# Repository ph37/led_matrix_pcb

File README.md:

# 32x16 LED Array PCB using 788BS

KiKad 5.1 files for the design of an LED matrix. The board has been manufactured by PCB Way and is
working.

The design is based around 788BS LED modules, which each contain 8x8 red LEDs in a common cathode
configuration.

While physically a 16 row and 32 column design, it is logically organised as 8 rows and 64
columns. Logical row N drives physical rows N and N+8.

Uses a 3-pin header to drive a series of 74HC595 shift registers. First shift register is connected to a 
74HC238 3-to-8 decoder to provide hardware enforced one-hot enable of rows. Rows are driven by a PMV16XN 
SMT power MOSFET to provide enough current to drive 32 LED columns.

Another eight 8-bit shift registers provide control over the 64 columns, with each column
using a 680 ohm resistor to limit current. Brightness of individual LEDs can be supported
externally by reprogramming the shift register and pulse-width-modulating the on-time for
each column.

## Notes

Board layout is intended for manufacture by PCB Way and follows PCB Way design rules. Please check
compatibility with design rules for any other PCB house.

Board is a very basic design and intended for low frequency operation only. In particular there is
no ground plane, which I plan to include in a future revision.

Take care with 788BS parts, I recommend testing them before soldering onto the board. 
The first board I've built has a short circuit inside one of 788BS components, are these 
are difficult to remove as the pins are underneath the package.

## Errata

v01 of the board transposed rows 6 and 7 on the included 788BS symbol. This can be resolved
by transposing the data for these rows in software before driving the serial interface.

## Future

I plan to release C drivers for Paspberry Pi Pico. Eventually I plan to migrate the IO the Pico's
programmable IO.

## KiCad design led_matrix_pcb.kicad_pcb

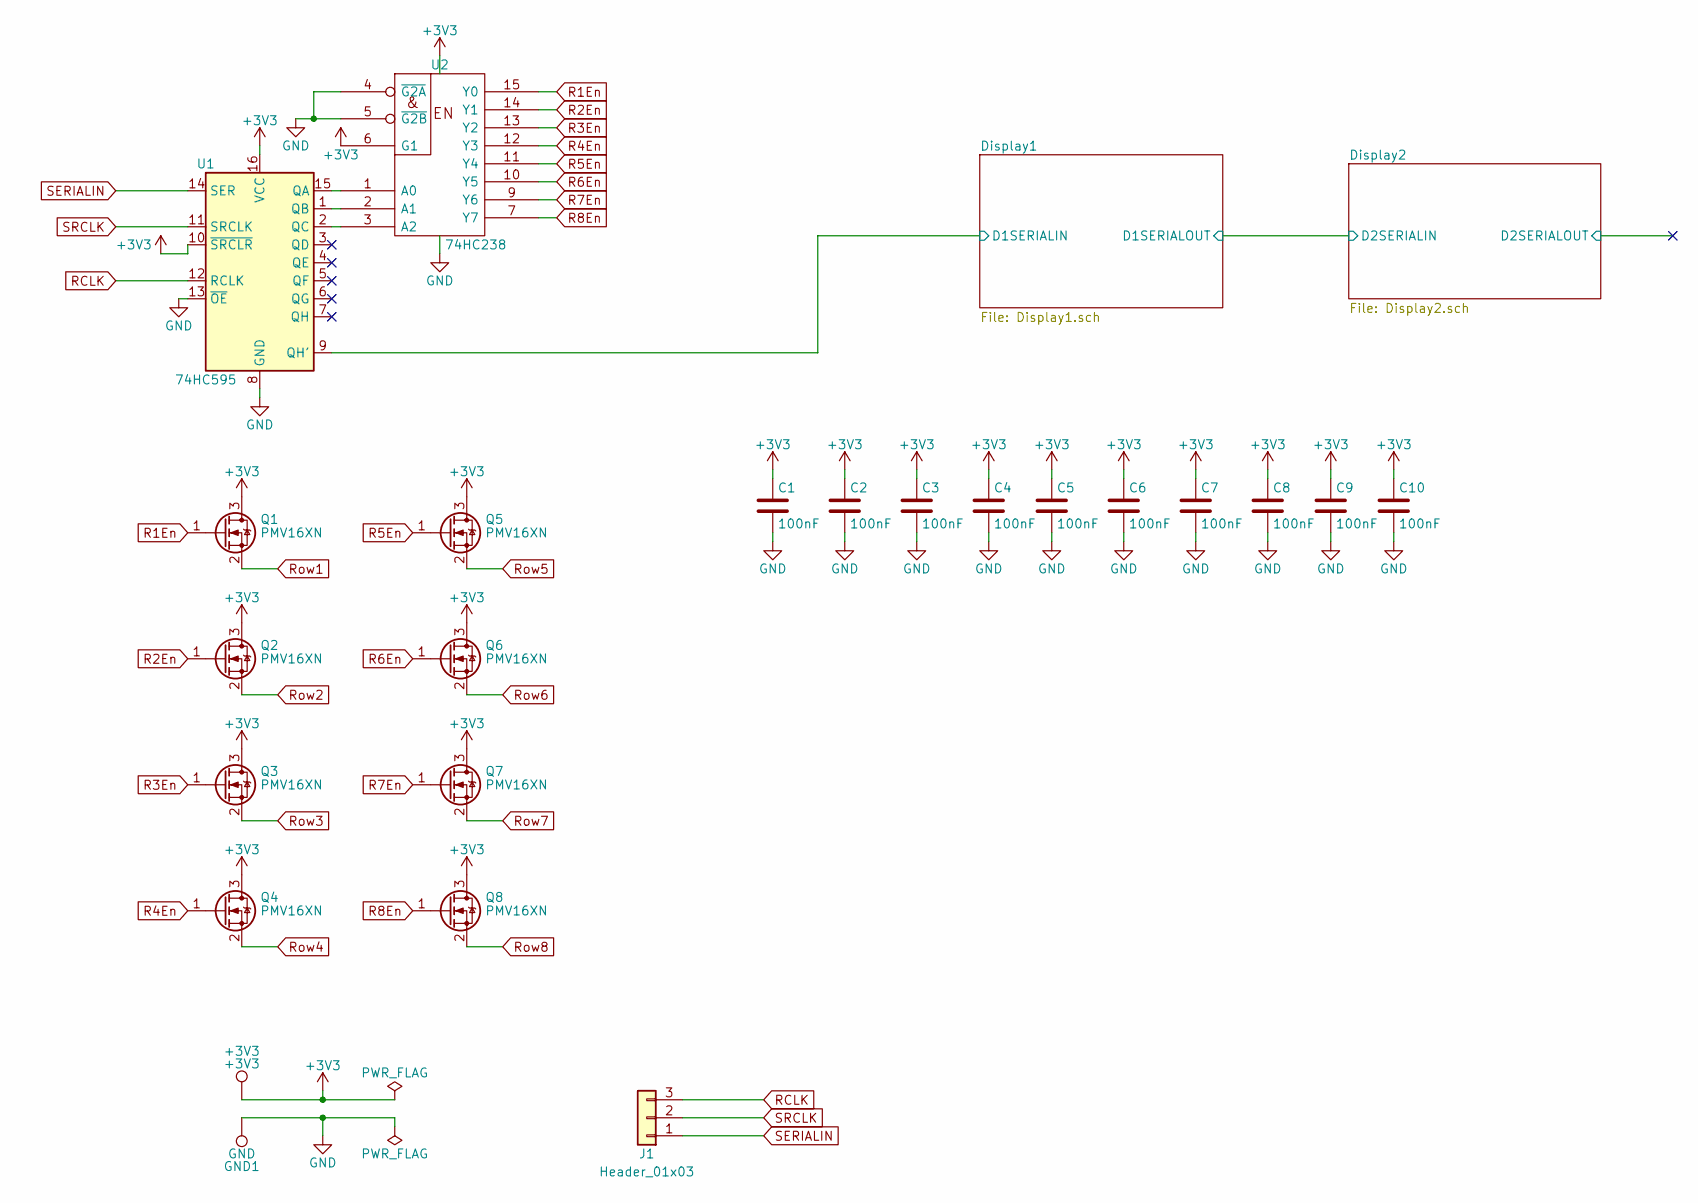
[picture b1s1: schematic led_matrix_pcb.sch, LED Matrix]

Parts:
+3V3: +3V3; TestPoint_Pad_D4.0mm
C1, C2, C3, C4, C5, C6, C7, C8, C9, C10: 100nF; C_Disc_D10.0mm_W2.5mm_P5.00mm
GND1: GND; TestPoint_Pad_D4.0mm
J1: Header_01x03; PinHeader_1x03_P2.54mm_Vertical
Q1, Q2, Q3, Q4, Q5, Q6, Q7, Q8: PMV16XN; SOT-23
U1: 74HC595; DIP-16_W7.62mm
U2: 74HC238; DIP-16_W7.62mm

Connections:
+3V3: +3V3.1, C1.1, C2.1, C3.1, C4.1, C5.1, C6.1, C7.1, C8.1, C9.1, C10.1, Q1.3 (D), Q2.3 (D), Q3.3 (D), Q4.3 (D), Q5.3 (D), Q6.3 (D), Q7.3 (D), Q8.3 (D), U1.10 (~SRCLR), U1.16 (VCC), U2.6 (G1), U2.16 (VCC); also elsewhere on the board
/Display1/D1SERIALIN: U1.9 (QH'); also elsewhere on the board
GND: C1.2, C2.2, C3.2, C4.2, C5.2, C6.2, C7.2, C8.2, C9.2, C10.2, GND1.1, U1.8 (GND), U1.13 (~OE), U2.4 (~G2A), U2.5 (~G2B), U2.8 (GND); also elsewhere on the board
unnamed: U1.1 (QB), U2.2 (A1)
unnamed: U1.2 (QC), U2.3 (A2)
unnamed: U1.15 (QA), U2.1 (A0)
R1En: Q1.1 (G), U2.15 (Y0)
R2En: Q2.1 (G), U2.14 (Y1)
R3En: Q3.1 (G), U2.13 (Y2)
R4En: Q4.1 (G), U2.12 (Y3)
R5En: Q5.1 (G), U2.11 (Y4)
R6En: Q6.1 (G), U2.10 (Y5)
R7En: Q7.1 (G), U2.9 (Y6)
R8En: Q8.1 (G), U2.7 (Y7)
RCLK: J1.3, U1.12 (RCLK); also elsewhere on the board
Row1: Q1.2 (S); also elsewhere on the board
Row2: Q2.2 (S); also elsewhere on the board
Row3: Q3.2 (S); also elsewhere on the board
Row4: Q4.2 (S); also elsewhere on the board
Row5: Q5.2 (S); also elsewhere on the board
Row6: Q6.2 (S); also elsewhere on the board
Row7: Q7.2 (S); also elsewhere on the board
Row8: Q8.2 (S); also elsewhere on the board
SERIALIN: J1.1, U1.14 (SER)
SRCLK: J1.2, U1.11 (SRCLK); also elsewhere on the board

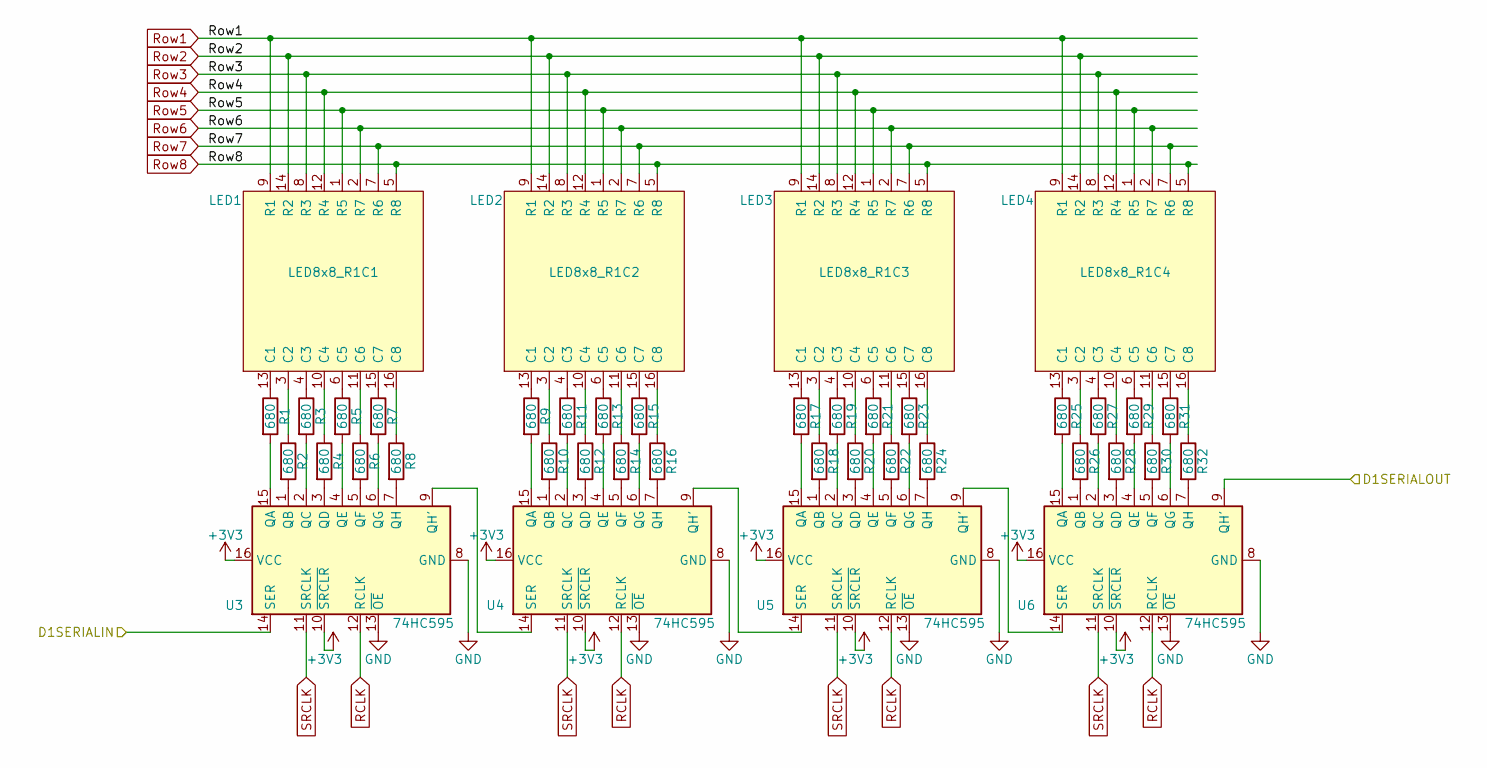
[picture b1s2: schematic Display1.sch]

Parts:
LED1: LED8x8_R1C1; 788BS
LED2: LED8x8_R1C2; 788BS
LED3: LED8x8_R1C3; 788BS
LED4: LED8x8_R1C4; 788BS
R1, R2, R3, R4, R5, R6, R7, R8, R9, R10, R11, R12, R13, R14, R15, R16, R17, R18, R19, R20, R21, R22, R23, R24, R25, R26, R27, R28, R29, R30, R31, R32: 680; R_Axial_DIN0204_L3.6mm_D1.6mm_P5.08mm_Horizontal
U3, U4, U5, U6: 74HC595; DIP-16_W7.62mm

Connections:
+3V3: U3.10 (~SRCLR), U3.16 (VCC), U4.10 (~SRCLR), U4.16 (VCC), U5.10 (~SRCLR), U5.16 (VCC), U6.10 (~SRCLR), U6.16 (VCC); also elsewhere on the board
/Display1/D1SERIALIN: U3.14 (SER); also elsewhere on the board
/Display1/D1SERIALOUT: U6.9 (QH'); also elsewhere on the board
GND: U3.8 (GND), U3.13 (~OE), U4.8 (GND), U4.13 (~OE), U5.8 (GND), U5.13 (~OE), U6.8 (GND), U6.13 (~OE); also elsewhere on the board
unnamed: LED1.3 (C2), R2.1
unnamed: LED1.4 (C3), R3.1
unnamed: LED1.6 (C5), R5.1
unnamed: LED1.10 (C4), R4.1
unnamed: LED1.11 (C6), R6.1
unnamed: LED1.13 (C1), R1.1
unnamed: LED1.15 (C7), R7.1
unnamed: LED1.16 (C8), R8.1
unnamed: LED2.3 (C2), R10.1
unnamed: LED2.4 (C3), R11.1
unnamed: LED2.6 (C5), R13.1
unnamed: LED2.10 (C4), R12.1
unnamed: LED2.11 (C6), R14.1
unnamed: LED2.13 (C1), R9.1
unnamed: LED2.15 (C7), R15.1
unnamed: LED2.16 (C8), R16.1
unnamed: LED3.3 (C2), R18.1
unnamed: LED3.4 (C3), R19.1
unnamed: LED3.6 (C5), R21.1
unnamed: LED3.10 (C4), R20.1
unnamed: LED3.11 (C6), R22.1
unnamed: LED3.13 (C1), R17.1
unnamed: LED3.15 (C7), R23.1
unnamed: LED3.16 (C8), R24.1
unnamed: LED4.3 (C2), R26.1
unnamed: LED4.4 (C3), R27.1
unnamed: LED4.6 (C5), R29.1
unnamed: LED4.10 (C4), R28.1
unnamed: LED4.11 (C6), R30.1
unnamed: LED4.13 (C1), R25.1
unnamed: LED4.15 (C7), R31.1
unnamed: LED4.16 (C8), R32.1
unnamed: R1.2, U3.15 (QA)
unnamed: R2.2, U3.1 (QB)
unnamed: R3.2, U3.2 (QC)
unnamed: R4.2, U3.3 (QD)
unnamed: R5.2, U3.4 (QE)
unnamed: R6.2, U3.5 (QF)
unnamed: R7.2, U3.6 (QG)
unnamed: R8.2, U3.7 (QH)
unnamed: R9.2, U4.15 (QA)
unnamed: R10.2, U4.1 (QB)
unnamed: R11.2, U4.2 (QC)
unnamed: R12.2, U4.3 (QD)
unnamed: R13.2, U4.4 (QE)
unnamed: R14.2, U4.5 (QF)
unnamed: R15.2, U4.6 (QG)
unnamed: R16.2, U4.7 (QH)
unnamed: R17.2, U5.15 (QA)
unnamed: R18.2, U5.1 (QB)
unnamed: R19.2, U5.2 (QC)
unnamed: R20.2, U5.3 (QD)
unnamed: R21.2, U5.4 (QE)
unnamed: R22.2, U5.5 (QF)
unnamed: R23.2, U5.6 (QG)
unnamed: R24.2, U5.7 (QH)
unnamed: R25.2, U6.15 (QA)
unnamed: R26.2, U6.1 (QB)
unnamed: R27.2, U6.2 (QC)
unnamed: R28.2, U6.3 (QD)
unnamed: R29.2, U6.4 (QE)
unnamed: R30.2, U6.5 (QF)
unnamed: R31.2, U6.6 (QG)
unnamed: R32.2, U6.7 (QH)
unnamed: U3.9 (QH'), U4.14 (SER)
unnamed: U4.9 (QH'), U5.14 (SER)
unnamed: U5.9 (QH'), U6.14 (SER)
RCLK: U3.12 (RCLK), U4.12 (RCLK), U5.12 (RCLK), U6.12 (RCLK); also elsewhere on the board
Row1: LED1.9 (R1), LED2.9 (R1), LED3.9 (R1), LED4.9 (R1); also elsewhere on the board
Row2: LED1.14 (R2), LED2.14 (R2), LED3.14 (R2), LED4.14 (R2); also elsewhere on the board
Row3: LED1.8 (R3), LED2.8 (R3), LED3.8 (R3), LED4.8 (R3); also elsewhere on the board
Row4: LED1.12 (R4), LED2.12 (R4), LED3.12 (R4), LED4.12 (R4); also elsewhere on the board
Row5: LED1.1 (R5), LED2.1 (R5), LED3.1 (R5), LED4.1 (R5); also elsewhere on the board
Row6: LED1.2 (R7), LED2.2 (R7), LED3.2 (R7), LED4.2 (R7); also elsewhere on the board
Row7: LED1.7 (R6), LED2.7 (R6), LED3.7 (R6), LED4.7 (R6); also elsewhere on the board
Row8: LED1.5 (R8), LED2.5 (R8), LED3.5 (R8), LED4.5 (R8); also elsewhere on the board
SRCLK: U3.11 (SRCLK), U4.11 (SRCLK), U5.11 (SRCLK), U6.11 (SRCLK); also elsewhere on the board

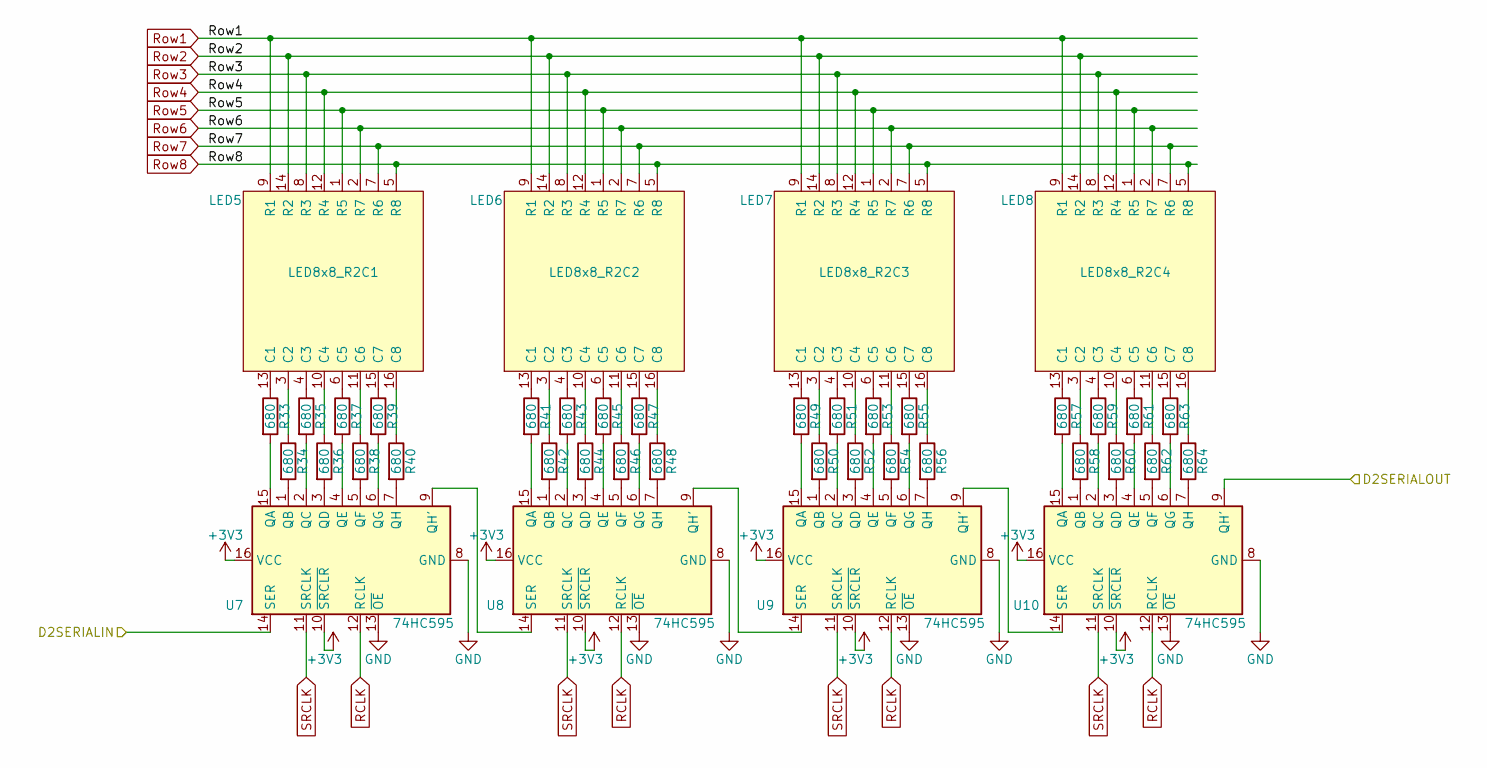
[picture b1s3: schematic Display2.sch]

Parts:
LED5: LED8x8_R2C1; 788BS
LED6: LED8x8_R2C2; 788BS
LED7: LED8x8_R2C3; 788BS
LED8: LED8x8_R2C4; 788BS
R33, R34, R35, R36, R37, R38, R39, R40, R41, R42, R43, R44, R45, R46, R47, R48, R49, R50, R51, R52, R53, R54, R55, R56, R57, R58, R59, R60, R61, R62, R63, R64: 680; R_Axial_DIN0204_L3.6mm_D1.6mm_P5.08mm_Horizontal
U7, U8, U9, U10: 74HC595; DIP-16_W7.62mm

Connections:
+3V3: U7.10 (~SRCLR), U7.16 (VCC), U8.10 (~SRCLR), U8.16 (VCC), U9.10 (~SRCLR), U9.16 (VCC), U10.10 (~SRCLR), U10.16 (VCC); also elsewhere on the board
/Display1/D1SERIALOUT: U7.14 (SER); also elsewhere on the board
/Display2/D2SERIALOUT: U10.9 (QH')
GND: U7.8 (GND), U7.13 (~OE), U8.8 (GND), U8.13 (~OE), U9.8 (GND), U9.13 (~OE), U10.8 (GND), U10.13 (~OE); also elsewhere on the board
unnamed: LED5.3 (C2), R34.1
unnamed: LED5.4 (C3), R35.1
unnamed: LED5.6 (C5), R37.1
unnamed: LED5.10 (C4), R36.1
unnamed: LED5.11 (C6), R38.1
unnamed: LED5.13 (C1), R33.1
unnamed: LED5.15 (C7), R39.1
unnamed: LED5.16 (C8), R40.1
unnamed: LED6.3 (C2), R42.1
unnamed: LED6.4 (C3), R43.1
unnamed: LED6.6 (C5), R45.1
unnamed: LED6.10 (C4), R44.1
unnamed: LED6.11 (C6), R46.1
unnamed: LED6.13 (C1), R41.1
unnamed: LED6.15 (C7), R47.1
unnamed: LED6.16 (C8), R48.1
unnamed: LED7.3 (C2), R50.1
unnamed: LED7.4 (C3), R51.1
unnamed: LED7.6 (C5), R53.1
unnamed: LED7.10 (C4), R52.1
unnamed: LED7.11 (C6), R54.1
unnamed: LED7.13 (C1), R49.1
unnamed: LED7.15 (C7), R55.1
unnamed: LED7.16 (C8), R56.1
unnamed: LED8.3 (C2), R58.1
unnamed: LED8.4 (C3), R59.1
unnamed: LED8.6 (C5), R61.1
unnamed: LED8.10 (C4), R60.1
unnamed: LED8.11 (C6), R62.1
unnamed: LED8.13 (C1), R57.1
unnamed: LED8.15 (C7), R63.1
unnamed: LED8.16 (C8), R64.1
unnamed: R33.2, U7.15 (QA)
unnamed: R34.2, U7.1 (QB)
unnamed: R35.2, U7.2 (QC)
unnamed: R36.2, U7.3 (QD)
unnamed: R37.2, U7.4 (QE)
unnamed: R38.2, U7.5 (QF)
unnamed: R39.2, U7.6 (QG)
unnamed: R40.2, U7.7 (QH)
unnamed: R41.2, U8.15 (QA)
unnamed: R42.2, U8.1 (QB)
unnamed: R43.2, U8.2 (QC)
unnamed: R44.2, U8.3 (QD)
unnamed: R45.2, U8.4 (QE)
unnamed: R46.2, U8.5 (QF)
unnamed: R47.2, U8.6 (QG)
unnamed: R48.2, U8.7 (QH)
unnamed: R49.2, U9.15 (QA)
unnamed: R50.2, U9.1 (QB)
unnamed: R51.2, U9.2 (QC)
unnamed: R52.2, U9.3 (QD)
unnamed: R53.2, U9.4 (QE)
unnamed: R54.2, U9.5 (QF)
unnamed: R55.2, U9.6 (QG)
unnamed: R56.2, U9.7 (QH)
unnamed: R57.2, U10.15 (QA)
unnamed: R58.2, U10.1 (QB)
unnamed: R59.2, U10.2 (QC)
unnamed: R60.2, U10.3 (QD)
unnamed: R61.2, U10.4 (QE)
unnamed: R62.2, U10.5 (QF)
unnamed: R63.2, U10.6 (QG)
unnamed: R64.2, U10.7 (QH)
unnamed: U7.9 (QH'), U8.14 (SER)
unnamed: U8.9 (QH'), U9.14 (SER)
unnamed: U9.9 (QH'), U10.14 (SER)
RCLK: U7.12 (RCLK), U8.12 (RCLK), U9.12 (RCLK), U10.12 (RCLK); also elsewhere on the board
Row1: LED5.9 (R1), LED6.9 (R1), LED7.9 (R1), LED8.9 (R1); also elsewhere on the board
Row2: LED5.14 (R2), LED6.14 (R2), LED7.14 (R2), LED8.14 (R2); also elsewhere on the board
Row3: LED5.8 (R3), LED6.8 (R3), LED7.8 (R3), LED8.8 (R3); also elsewhere on the board
Row4: LED5.12 (R4), LED6.12 (R4), LED7.12 (R4), LED8.12 (R4); also elsewhere on the board
Row5: LED5.1 (R5), LED6.1 (R5), LED7.1 (R5), LED8.1 (R5); also elsewhere on the board
Row6: LED5.2 (R7), LED6.2 (R7), LED7.2 (R7), LED8.2 (R7); also elsewhere on the board
Row7: LED5.7 (R6), LED6.7 (R6), LED7.7 (R6), LED8.7 (R6); also elsewhere on the board
Row8: LED5.5 (R8), LED6.5 (R8), LED7.5 (R8), LED8.5 (R8); also elsewhere on the board
SRCLK: U7.11 (SRCLK), U8.11 (SRCLK), U9.11 (SRCLK), U10.11 (SRCLK); also elsewhere on the board

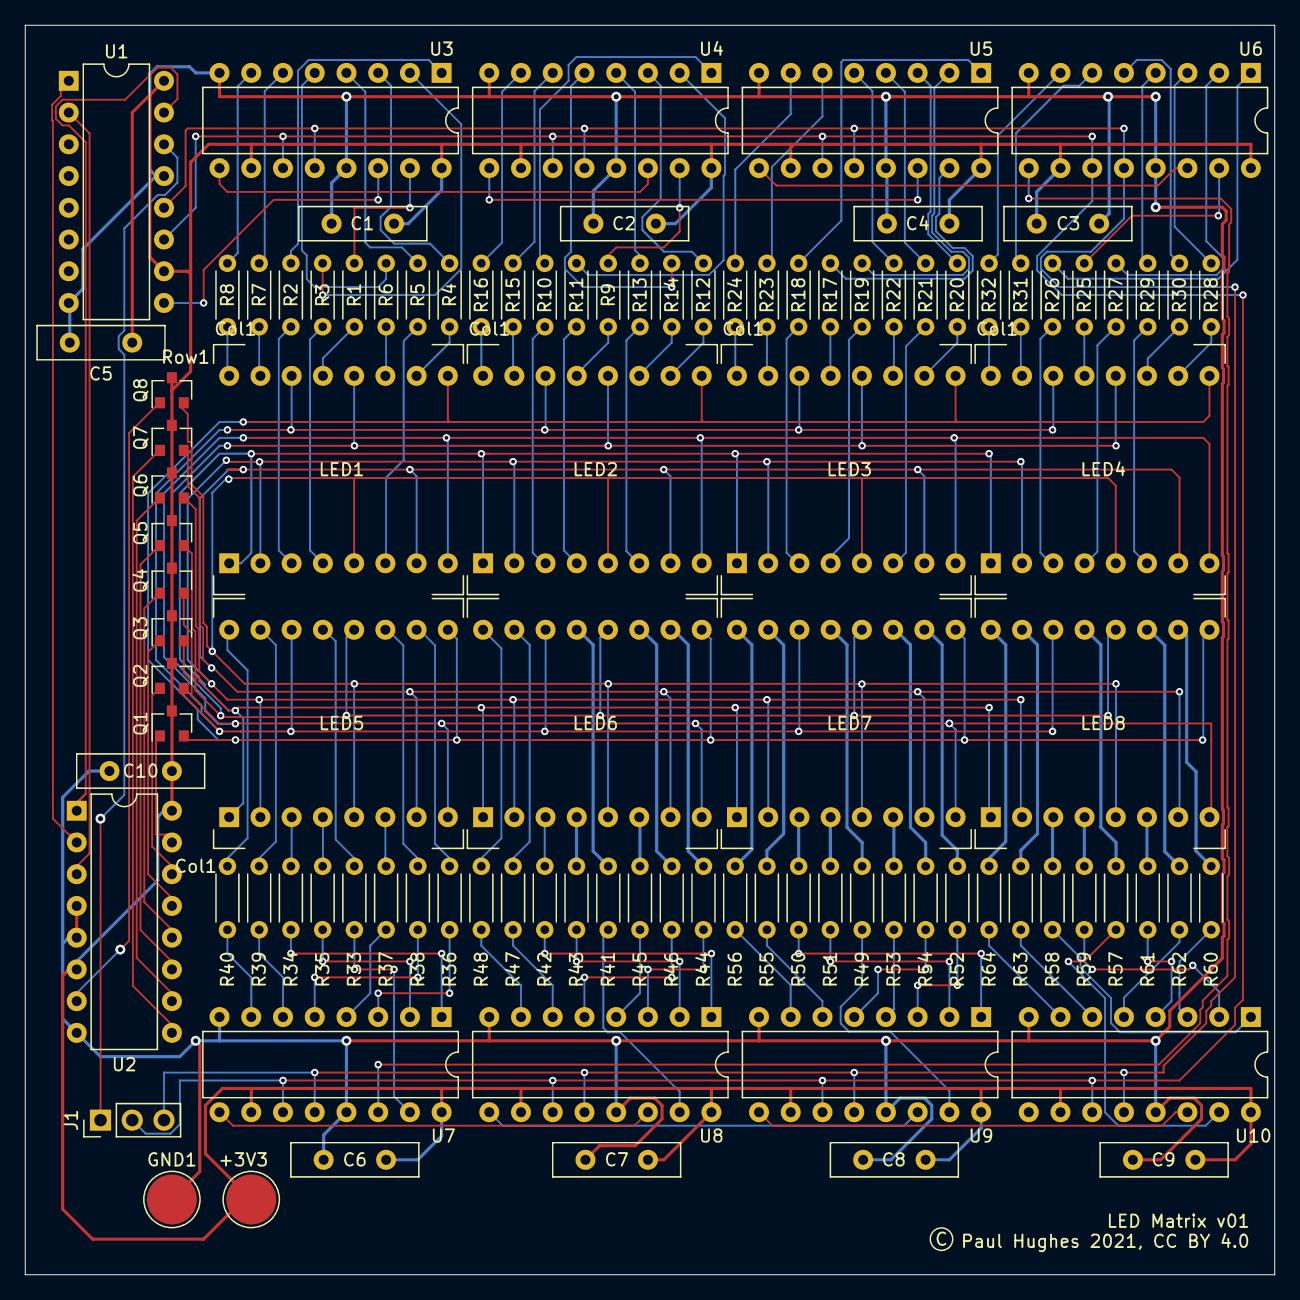
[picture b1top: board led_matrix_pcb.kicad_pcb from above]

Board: 2 copper layers, 100.0 x 100.0 mm, 103 parts (0 on the bottom side), 160 nets.

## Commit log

2022-02-12 Initial commit of led_matrix_pcb
    Initial commit of files with modifications to support
    open source release. Includes necessary libraries.
2022-02-12 Fix library name in LED8x8 instances in schematic
2022-02-12 Added rendering of PCB for README
2022-02-12 Fix typo
2022-02-12 Added supported KiCad version
2022-02-12 Added info on 788BS
2022-02-13 Typo in README.md errata description
2022-02-20 Small additions to README

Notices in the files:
led_matrix_pcb.kicad_pcb:
Paul Hughes 2021, CC BY 4.0
led_matrix_pcb.sch:
CC-BY-4.0
© Paul Hughes 2021
